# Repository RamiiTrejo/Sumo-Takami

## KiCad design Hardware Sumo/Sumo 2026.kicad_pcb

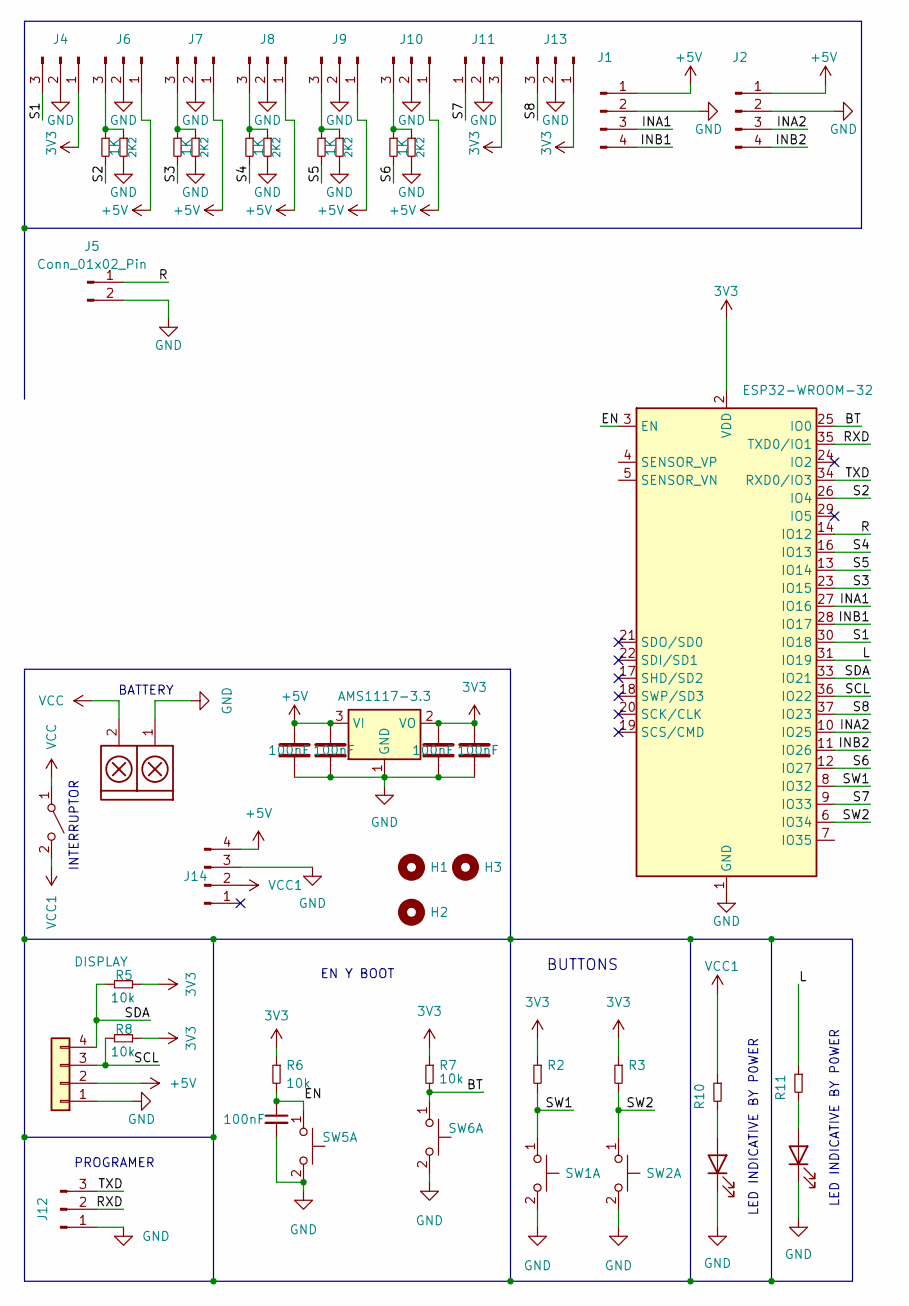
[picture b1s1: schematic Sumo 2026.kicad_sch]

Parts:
Alimentacion1: TB_1X2; AMASS_XT30U-M_1x02_P5.0mm_Vertical
C3, C4, C6, C7, C8: 100nF; C_0805_2012Metric_Pad1.18x1.45mm_HandSolder
D2, D3: LED; LED_0805_2012Metric_Pad1.15x1.40mm_HandSolder
H1, H2, H3: MountingHole; MountingHole_3mm
J1, J2: Conn_01x04_Pin; JST_XH_B4B-XH-A_1x04_P2.50mm_Vertical
J3: DISPLAY; PinSocket_1x04_P2.54mm_Vertical
J4, J6, J7, J8, J9, J10, J11, J13: Conn_01x03_Pin; JST_XH_B3B-XH-A_1x03_P2.50mm_Vertical
J5: Conn_01x02_Pin; JST_XH_B2B-XH-A_1x02_P2.50mm_Vertical
J12: Conn_01x03_Pin; PinHeader_1x03_P2.54mm_Vertical
J14: Conn_01x04_Pin; Step_Down_Mini
R2, R3, R5, R6, R7, R8, R10: 10k; R_0805_2012Metric_Pad1.20x1.40mm_HandSolder
R11: 10k; R_1206_3216Metric
R15, R18, R20, R22, R24: 1K; R_1206_3216Metric_Pad1.30x1.75mm_HandSolder
R17, R19, R21, R23, R25: 2K2; R_1206_3216Metric_Pad1.30x1.75mm_HandSolder
SW1, SW5, SW6: SW_Push_Dual_x2; SW SMD 3.5X6X5
SW2: SW SMD 3.5X6X5
SWI1: SW_DPST_x2; Switch Slide
U1: AMS1117-3.3; SOT-223-3_TabPin2
U3: ESP32-WROOM-32

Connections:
3V3: C7.1, C8.1, J4.1, J11.3, J13.1, R2.1, R3.1, R5.1, R6.1, R7.1, R8.1, U1.2 (VO), U3.2 (VDD)
+5V: C3.1, C4.1, J1.1, J2.1, J3.2, J6.1, J7.1, J8.1, J9.1, J10.1, J14.4, U1.3 (VI)
/BT: R7.2, SW6.1 (C), U3.25 (IO0)
/EN: C6.1, R6.2, SW5.1 (C), U3.3 (EN)
/INA1: J1.3, U3.27 (IO16)
/INA2: J2.3, U3.10 (IO25)
/INB1: J1.4, U3.28 (IO17)
/INB2: J2.4, U3.11 (IO26)
/L: R11.1, U3.31 (IO19)
/R: J5.1, U3.14 (IO12)
/RXD: J12.2, U3.35 (TXD0/IO1)
/S1: J4.3, U3.30 (IO18)
/S2: R15.2, U3.26 (IO4)
/S3: R18.2, U3.23 (IO15)
/S4: R20.2, U3.16 (IO13)
/S5: R22.2, U3.13 (IO14)
/S6: R24.2, U3.12 (IO27)
/S7: J11.1, U3.9 (IO33)
/S8: J13.3, U3.37 (IO23)
/SCL: J3.3, R8.2, U3.36 (IO22)
/SDA: J3.4, R5.2, U3.33 (IO21)
/SW1: R2.2, SW1.1 (C), U3.8 (IO32)
/SW2: R3.2, SW2.1 (C), U3.6 (IO34)
/TXD: J12.3, U3.34 (RXD0/IO3)
GND: Alimentacion1.1, C3.2, C4.2, C6.2, C7.2, C8.2, D2.1 (K), D3.1 (K), J1.2, J2.2, J3.1, J4.2, J5.2, J6.2, J7.2, J8.2, J9.2, J10.2, J11.2, J12.1, J13.2, J14.3, R17.2, R19.2, R21.2, R23.2, R25.2, SW1.2 (D), SW2.2 (D), SW5.2 (D), SW6.2 (D), U1.1 (GND), U3.1 (GND), U3.15 (GND), U3.38 (GND), U3.39 (GND)
unnamed: D2.2 (A), R10.2
unnamed: D3.2 (A), R11.2
unnamed: J6.3, R15.1, R17.1
unnamed: J7.3, R18.1, R19.1
unnamed: J8.3, R20.1, R21.1
unnamed: J9.3, R22.1, R23.1
unnamed: J10.3, R24.1, R25.1
VCC: Alimentacion1.2, SWI1.1 (A)
VCC1: J14.2, R10.1, SWI1.2 (B)

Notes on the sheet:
EN Y BOOT
PROGRAMER
LED INDICATIVE BY P0WER
BUTTONS
BATTERY
INTERRUPTOR

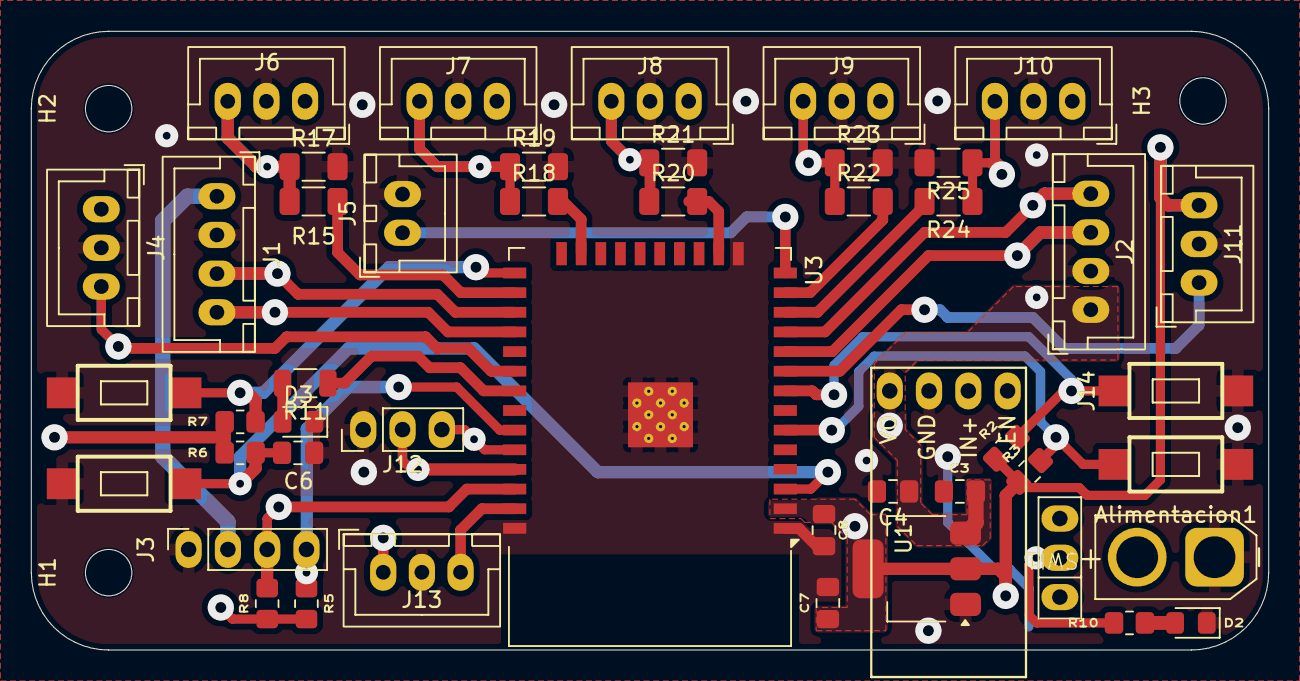
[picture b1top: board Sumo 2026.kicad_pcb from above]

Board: 2 copper layers, 80.0 x 40.0 mm, 50 parts (0 on the bottom side), 34 nets.
